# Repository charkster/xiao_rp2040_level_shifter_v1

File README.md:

# xiao_rp2040_level_shifter_v1
Add-on PCB board for Seeed Studio Xiao RP2040, using NVT2010PW level shifter and on-board 1.2V and 1.8V LDO regulators. An external VREFA may be driven (no jumper) to a custom voltage 2.5V or below. The NVT2010PW level shifter allows VREFA voltages as low as 0.9V.

Check-out my **PDF** [schematic](https://github.com/charkster/xiao_rp2040_level_shifter_v1/blob/main/xiao_rp2040_level_shifter_v1_schematic.pdf) !!

Check-out the CSV [**Bill of Materials**](https://github.com/charkster/xiao_rp2040_level_shifter_v1/blob/main/xiao_rp2040_level_shifter_v1_BOM.csv) !!

Pin 1 of J1 is bottom left (it is rotated 90 deg CCW).

2x10 2.54mm stacking headers can be found on [Aliexpress](https://www.aliexpress.us/item/2251832794527968.html?gatewayAdapt=glo2usa4itemAdapt&_randl_shipto=US)

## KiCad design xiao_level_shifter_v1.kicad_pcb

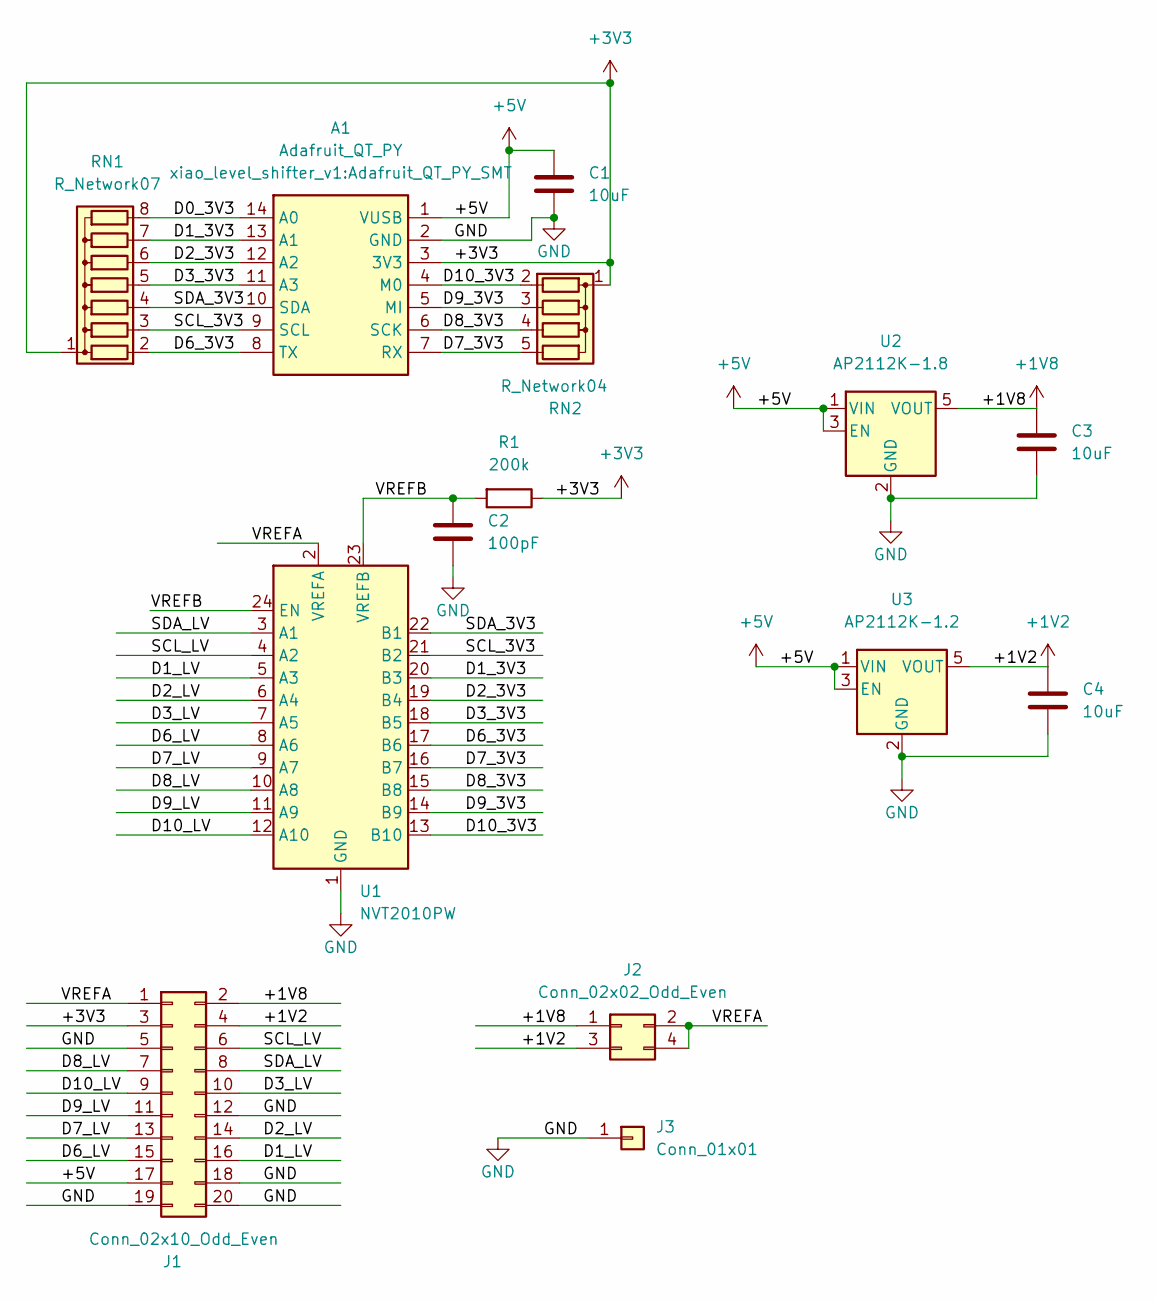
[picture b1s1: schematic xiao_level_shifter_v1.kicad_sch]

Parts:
A1: Adafruit_QT_PY; Adafruit_QT_PY_SMT
C1, C3, C4: 10uF; R_0603_1608Metric
C2: 100pF; R_0603_1608Metric
J1: Conn_02x10_Odd_Even; PinHeader_2x10_P2.54mm_Vertical
J2: Conn_02x02_Odd_Even; PinHeader_2x02_P2.54mm_Vertical
J3: Conn_01x01; PinHeader_1x01_P2.54mm_Vertical
R1: 200k; C_0603_1608Metric
RN1: R_Network07; R_Array_SMT8
RN2: R_Network04; R_Array_SMT5
U1: NVT2010PW; TSSOP-24_4.4x7.8mm_P0.65mm
U2: AP2112K-1.8; SOT-23-5
U3: AP2112K-1.2; SOT-23-5

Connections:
+1V2: C4.1, J1.4, J2.3, U3.5 (VOUT)
+1V8: C3.1, J1.2, J2.1, U2.5 (VOUT)
+3V3: A1.3 (3V3), J1.3, R1.1, RN1.1 (common), RN2.1 (common)
+5V: A1.1 (VUSB), C1.1, J1.17, U2.1 (VIN), U2.3 (EN), U3.1 (VIN), U3.3 (EN)
/D0_3V3: A1.14 (A0), RN1.8 (R7)
/D1_3V3: A1.13 (A1), RN1.7 (R6), U1.20 (B3)
/D1_LV: J1.16, U1.5 (A3)
/D2_3V3: A1.12 (A2), RN1.6 (R5), U1.19 (B4)
/D2_LV: J1.14, U1.6 (A4)
/D3_3V3: A1.11 (A3), RN1.5 (R4), U1.18 (B5)
/D3_LV: J1.10, U1.7 (A5)
/D6_3V3: A1.8 (TX), RN1.2 (R1), U1.17 (B6)
/D6_LV: J1.15, U1.8 (A6)
/D7_3V3: A1.7 (RX), RN2.5 (R4), U1.16 (B7)
/D7_LV: J1.13, U1.9 (A7)
/D8_3V3: A1.6 (SCK), RN2.4 (R3), U1.15 (B8)
/D8_LV: J1.7, U1.10 (A8)
/D9_3V3: A1.5 (MI), RN2.3 (R2), U1.14 (B9)
/D9_LV: J1.11, U1.11 (A9)
/D10_3V3: A1.4 (M0), RN2.2 (R1), U1.13 (B10)
/D10_LV: J1.9, U1.12 (A10)
/SCL_3V3: A1.9 (SCL), RN1.3 (R2), U1.21 (B2)
/SCL_LV: J1.6, U1.4 (A2)
/SDA_3V3: A1.10 (SDA), RN1.4 (R3), U1.22 (B1)
/SDA_LV: J1.8, U1.3 (A1)
/VREFA: J1.1, J2.2, J2.4, U1.2 (VREFA)
/VREFB: C2.1, R1.2, U1.23 (VREFB), U1.24 (EN)
GND: A1.2 (GND), C1.2, C2.2, C3.2, C4.2, J1.5, J1.12, J1.18, J1.19, J1.20, J3.1, U1.1 (GND), U2.2 (GND), U3.2 (GND)

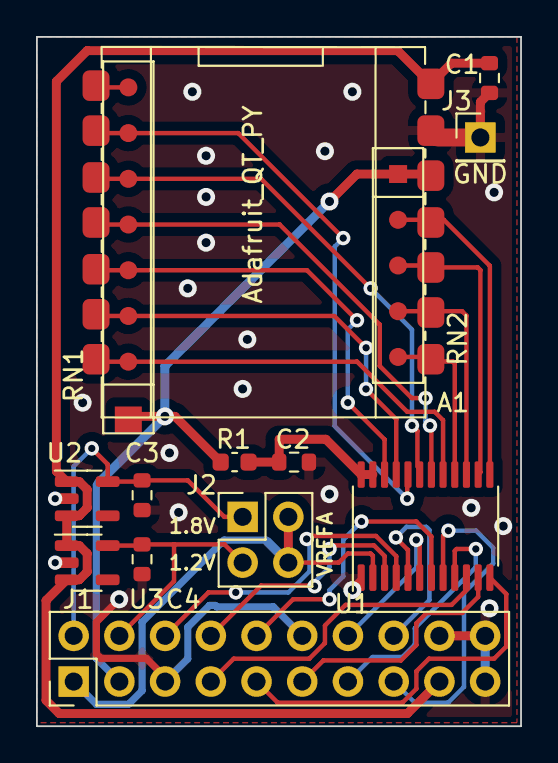
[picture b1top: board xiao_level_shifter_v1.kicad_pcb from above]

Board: 2 copper layers, 26.9 x 38.3 mm, 14 parts (0 on the bottom side), 28 nets.

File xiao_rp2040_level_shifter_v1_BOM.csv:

Source:,kicad/level_shifter_boards/xiao_level_shifter_v1/xiao_level_shifter_v1/xiao_level_shifter_v1.kicad_sch,,,,,
Date:,Mon 10 Apr 2023 08:45:29 PM MST,,,,,
Tool:,Eeschema 6.0.2+dfsg-1,,,,,
Generator:,/usr/share/kicad/plugins/bom_csv_grouped_by_value.py,,,,,
Component Count:,14,,,,,
,,,,,,
Individual Components:,,,,,,
,,,,,,
Item,Qty,Reference(s),Value,LibPart,Footprint,Datasheet
,,A1,Adafruit_QT_PY,xiao_level_shifter_v1:Adafruit_QT_PY,xiao_level_shifter_v1:Adafruit_QT_PY_SMT,https://www.adafruit.com/product/4600
,,C1,10uF,Device:C,Resistor_SMD:R_0603_1608Metric,~
,,C2,100pF,Device:C,Resistor_SMD:R_0603_1608Metric,~
,,C3,10uF,Device:C,Resistor_SMD:R_0603_1608Metric,~
,,C4,10uF,Device:C,Resistor_SMD:R_0603_1608Metric,~
,,J1,Conn_02x10_Odd_Even,Connector_Generic:Conn_02x10_Odd_Even,Connector_PinHeader_2.54mm:PinHeader_2x10_P2.54mm_Vertical,~
,,J2,Conn_02x02_Odd_Even,Connector_Generic:Conn_02x02_Odd_Even,Connector_PinHeader_2.54mm:PinHeader_2x02_P2.54mm_Vertical,~
,,J3,Conn_01x01,Connector_Generic:Conn_01x01,Connector_PinHeader_2.54mm:PinHeader_1x01_P2.54mm_Vertical,~
,,R1,200k,Device:R,Capacitor_SMD:C_0603_1608Metric,~
,,RN1,R_Network07,Device:R_Network07,xiao_level_shifter_v1:R_Array_SMT8,http://www.vishay.com/docs/31509/csc.pdf
,,RN2,R_Network04,Device:R_Network04,xiao_level_shifter_v1:R_Array_SMT5,http://www.vishay.com/docs/31509/csc.pdf
,,U1,NVT2010PW,xiao_level_shifter_v1:NVT2010PW,Package_SO:TSSOP-24_4.4x7.8mm_P0.65mm,https://www.nxp.com/docs/en/data-sheet/NVT2008_NVT2010.pdf
,,U2,AP2112K-1.8,Regulator_Linear:AP2112K-1.8,Package_TO_SOT_SMD:SOT-23-5,https://www.diodes.com/assets/Datasheets/AP2112.pdf
,,U3,AP2112K-1.2,Regulator_Linear:AP2112K-1.2,Package_TO_SOT_SMD:SOT-23-5,https://www.diodes.com/assets/Datasheets/AP2112.pdf
,,,,,,
,,,,,,
,,,,,,
Collated Components:,,,,,,
,,,,,,
Item,Qty,Reference(s),Value,LibPart,Footprint,Datasheet
1,1,A1,Adafruit_QT_PY,xiao_level_shifter_v1:Adafruit_QT_PY,xiao_level_shifter_v1:Adafruit_QT_PY_SMT,https://www.adafruit.com/product/4600
2,3,"C1, C3, C4",10uF,Device:C,Resistor_SMD:R_0603_1608Metric,~
3,1,C2,100pF,Device:C,Resistor_SMD:R_0603_1608Metric,~
4,1,J1,Conn_02x10_Odd_Even,Connector_Generic:Conn_02x10_Odd_Even,Connector_PinHeader_2.54mm:PinHeader_2x10_P2.54mm_Vertical,~
5,1,J2,Conn_02x02_Odd_Even,Connector_Generic:Conn_02x02_Odd_Even,Connector_PinHeader_2.54mm:PinHeader_2x02_P2.54mm_Vertical,~
6,1,J3,Conn_01x01,Connector_Generic:Conn_01x01,Connector_PinHeader_2.54mm:PinHeader_1x01_P2.54mm_Vertical,~
7,1,R1,200k,Device:R,Capacitor_SMD:C_0603_1608Metric,~
8,1,RN1,R_Network07,Device:R_Network07,xiao_level_shifter_v1:R_Array_SMT8,http://www.vishay.com/docs/31509/csc.pdf
9,1,RN2,R_Network04,Device:R_Network04,xiao_level_shifter_v1:R_Array_SMT5,http://www.vishay.com/docs/31509/csc.pdf
10,1,U1,NVT2010PW,xiao_level_shifter_v1:NVT2010PW,Package_SO:TSSOP-24_4.4x7.8mm_P0.65mm,https://www.nxp.com/docs/en/data-sheet/NVT2008_NVT2010.pdf
11,1,U2,AP2112K-1.8,Regulator_Linear:AP2112K-1.8,Package_TO_SOT_SMD:SOT-23-5,https://www.diodes.com/assets/Datasheets/AP2112.pdf
12,1,U3,AP2112K-1.2,Regulator_Linear:AP2112K-1.2,Package_TO_SOT_SMD:SOT-23-5,https://www.diodes.com/assets/Datasheets/AP2112.pdf

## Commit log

2023-04-20 Create LICENSE
